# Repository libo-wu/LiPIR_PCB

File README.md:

# LiPIR_PCB
PCB files related to the LiPIR design

## LC driver board
	This board has three inputs: PWM 1 and PWM 2 from the external MCU; Vdd is from an 9V battery. 
	
	Two outputs: OUT1 and OUT2.
	
	PWM 1 and PWM 2 are PWM waveforms that out-of-phase with the frequency \[f\] around 100Hz. The outpout signal is an alternate current (AC) voltage with amplitute around 18V. 
	
	TO DO:
	
	1. Solder the board and use Arduino board to test the performance.
	2. Measure the power consumption.

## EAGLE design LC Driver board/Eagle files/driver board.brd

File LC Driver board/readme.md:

## Compoments:
1. P-MOSFET:   IRLML6401, [datasheet](https://www.infineon.com/dgdl/irlml6401pbf.pdf?fileId=5546d462533600a401535668b96d2634)
2. N_MOSFET:   IRLML2502, [datasheet](https://www.farnell.com/datasheets/1912230.pdf)
3. NPN transistor: BCW66, [datasheet](https://www.gme.cz/data/attachments/dsh.912-075.1.pdf)
4. POWER jack: PJ202A,    [datasheet](https://www.cuidevices.com/product/resource/pj-202a.pdf)

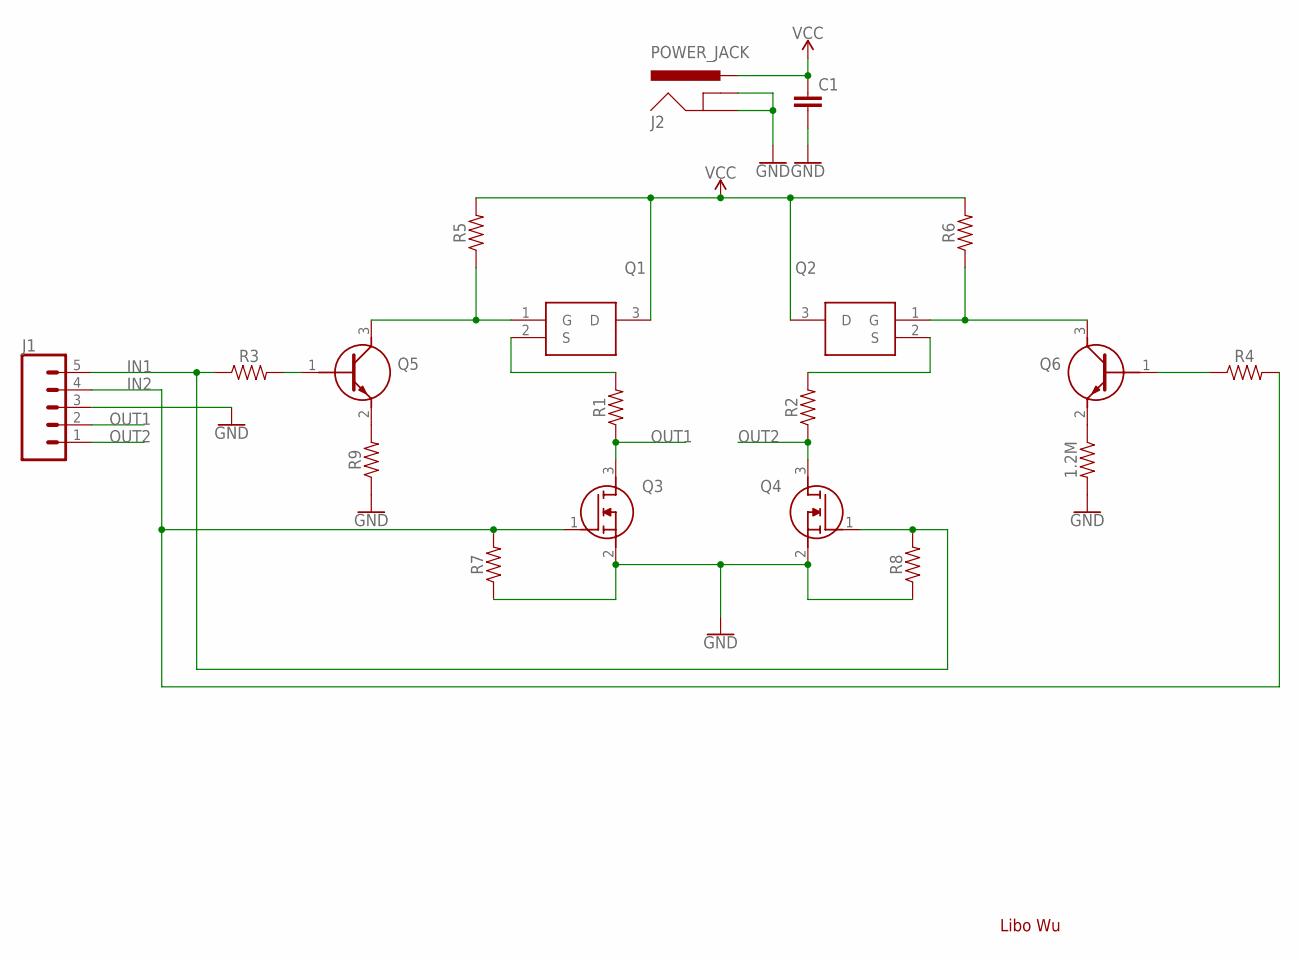
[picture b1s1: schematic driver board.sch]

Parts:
C1: 10nF; 0603
J1: CONN_05; 1X05
J2: POWER_JACK; POWER_JACK_PTH
Q1, Q2: IRLML6401TRPBF; SOT95P237X112-3N
Q3, Q4: IRLML2502TRPBF; SOT95P237X112-3N
Q5, Q6: BCW66HQTA; FMMT619TA
R1, R2, R3, R4, R5, R6, R7, R8, R9, R10: 1.2M; 0603

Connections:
GND: C1.2, J1.3, J2.GND, J2.GNDBREAK, Q3.2 (S), Q4.2 (S), R7.1, R8.1, R9.1, R10.2
IN1: J1.5, Q4.1 (G), R3.1, R8.2
IN2: J1.4, Q3.1 (G), R4.2, R7.2
unnamed: Q1.2 (S), R1.2
unnamed: Q2.2 (S), R2.2
unnamed: Q2.1 (G), Q6.3 (C), R6.1
unnamed: Q6.2 (E), R10.1
unnamed: Q6.1 (B), R4.1
unnamed: Q5.2 (E), R9.2
unnamed: Q1.1 (G), Q5.3 (C), R5.1
unnamed: Q5.1 (B), R3.2
OUT1: J1.2, Q3.3 (D), R1.1
OUT2: J1.1, Q4.3 (D), R2.1
VCC: C1.1, J2.PWR, Q1.3 (D), Q2.3 (D), R5.2, R6.2

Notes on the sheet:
Libo Wu

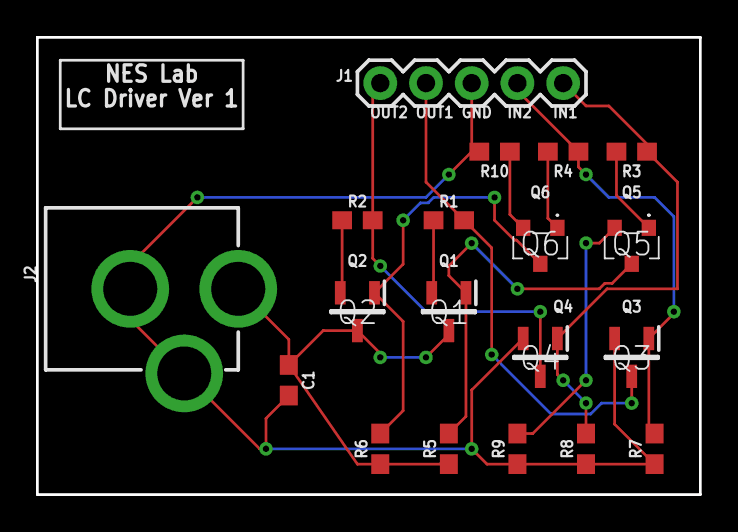
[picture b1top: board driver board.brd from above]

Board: 2 copper layers, 36.8 x 25.4 mm, 19 parts (0 on the bottom side), 14 nets.

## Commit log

2019-10-08 Driver board
2019-10-16 create readme.md for driving circuit
2019-10-22 Update arduino code

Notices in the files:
parts and their libraries:
SparkFun-Capacitors: Licensing: Creative Commons ShareAlike 4.0 International - https://creativecommons.org/licenses/by-sa/4.0
